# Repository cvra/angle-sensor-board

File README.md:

# Carte Codeur Absolu

## Cahier des charges

### Général

* Le but de cette carte est de fournir une information de position angulaire absolue, c'est-à-dire un angle par rapport à une position de référence.
* La carte se connecte à une carte moteur CVRA pour en augmenter les capacités.
* La carte fournit 4096 points par tour.
* La carte est assemblable à la main, mais peut nécessiter un pochoir pour les composants SMD.

### Electronique

* Alimentation: 20mA @ 3.3V.
* Connection compatible avec le connecteur de la carte moteur (P3 sur [ce schéma](https://github.com/cvra/motor-control-board/raw/revA/Moteur.pdf).
* Interface SPI.
* Branchement par un connecteur PicoBlade 5 pin.
* LED pour indiquer l’alimentation.
* Respecte les [design rules Aisler](https://aisler.net/help/design-rules-and-specifications/design-rules).
* Taille des passifs: 0603.

## Mécanique

* le plus petit possible (13mmx11mm)
* 2x demi trous M2 sur bord opposée
* connecteur sortie parallèle au PCB, sur face opposée au capteur
* LED sur la même face que le connecteur
* Capteur centré au milieux des vis

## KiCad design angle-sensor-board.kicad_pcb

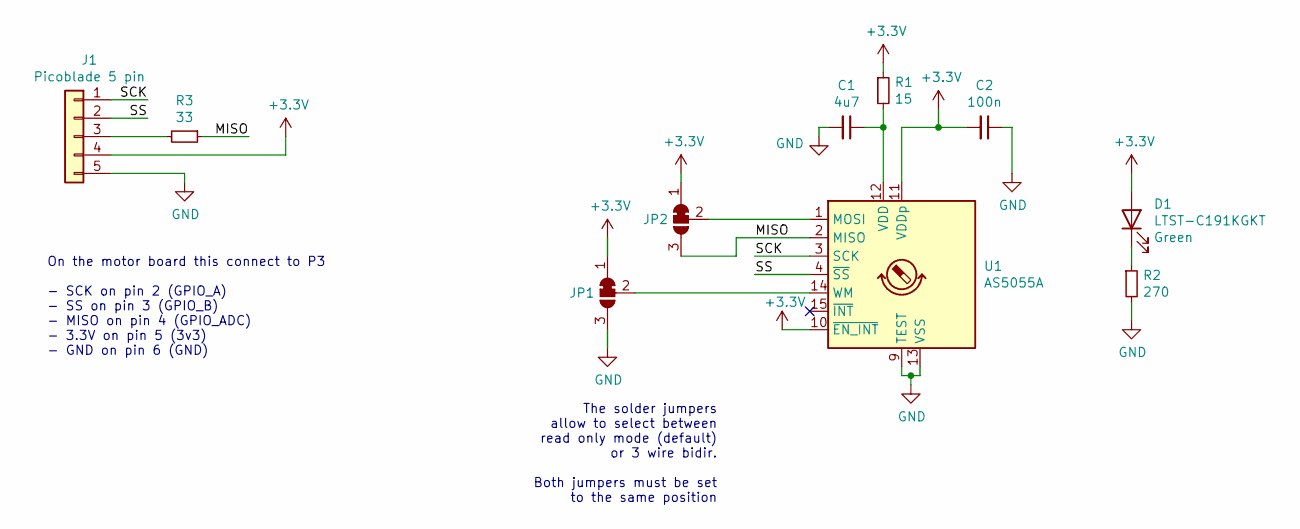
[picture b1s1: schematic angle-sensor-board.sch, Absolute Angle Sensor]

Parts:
C1: 4u7; C_0603_1608Metric_Pad1.08x0.95mm_HandSolder; digikey# 1276-1045-1-ND
C2: 100n; C_0603_1608Metric_Pad1.08x0.95mm_HandSolder; digikey# 1276-1006-1-ND
D1: LTST-C191KGKT; LED_0603_1608Metric_Castellated; digikey# 160-1446-1-ND
J1: Picoblade 5 pin; Molex_PicoBlade_53261-0571_1x05-1MP_P1.25mm_Horizontal; digikey# WM7623CT-ND
JP1, JP2: SolderJumper_3_Bridged12; SolderJumper-3_P1.3mm_Bridged12_RoundedPad1.0x1.5mm
R1: 15; R_0603_1608Metric_Pad0.98x0.95mm_HandSolder; digikey# A129666CT-ND
R2: 270; R_0603_1608Metric_Pad0.98x0.95mm_HandSolder; digikey# A129681CT-ND
R3: 33; R_0603_1608Metric_Pad0.98x0.95mm_HandSolder; digikey# A130082CT-ND
U1: AS5055A; QFN-16-1EP_4x4mm_P0.65mm_EP2.7x2.7mm; digikey# AS5055A-BQFMCT-ND

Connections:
+3V3: C2.2, D1.2 (A), J1.4, JP1.1 (A), JP2.1 (A), R1.1, U1.10 (~EN_INT), U1.11 (VDDp)
/MISO: JP2.3 (B), R3.1, U1.2 (MISO)
/SCK: J1.1, U1.3 (SCK)
/SS: J1.2, U1.4 (~SS)
GND: C1.2, C2.1, J1.5, JP1.3 (B), R2.2, U1.9 (TEST), U1.13 (VSS)
unnamed: C1.1, R1.2, U1.12 (VDD)
unnamed: D1.1 (K), R2.1
unnamed: J1.3, R3.2
unnamed: JP1.2 (C), U1.14 (WM)
unnamed: JP2.2 (C), U1.1 (MOSI)

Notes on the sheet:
On the motor board this connect to P3 - SCK on pin 2 (GPIO_A) - SS on pin 3 (GPIO_B) - MISO on pin 4 (GPIO_ADC) - 3.3V on pin 5 (3v3) - GND on pin 6 (GND)
The solder jumpers allow to select between read only mode (default) or 3 wire bidir. Both jumpers must be set to the same position

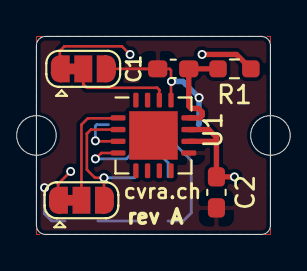
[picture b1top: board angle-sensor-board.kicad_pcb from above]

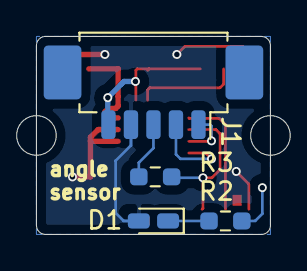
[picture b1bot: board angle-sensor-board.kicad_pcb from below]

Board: 2 copper layers, 13.0 x 11.0 mm, 10 parts (4 on the bottom side), 10 nets.

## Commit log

2021-11-28 Add .gitignore
2021-11-28 Initial design
2021-11-28 Add a README with the features
2021-12-02 Add digikey references for passives
2021-12-10 Add some solder jumpers to select modes
2021-12-10 Add production output files
2021-12-10 Add missing prod files
2022-01-15 Add some test software to check if the PCBs are working

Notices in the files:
angle-sensor-board.sch:
CC-BY-SA
